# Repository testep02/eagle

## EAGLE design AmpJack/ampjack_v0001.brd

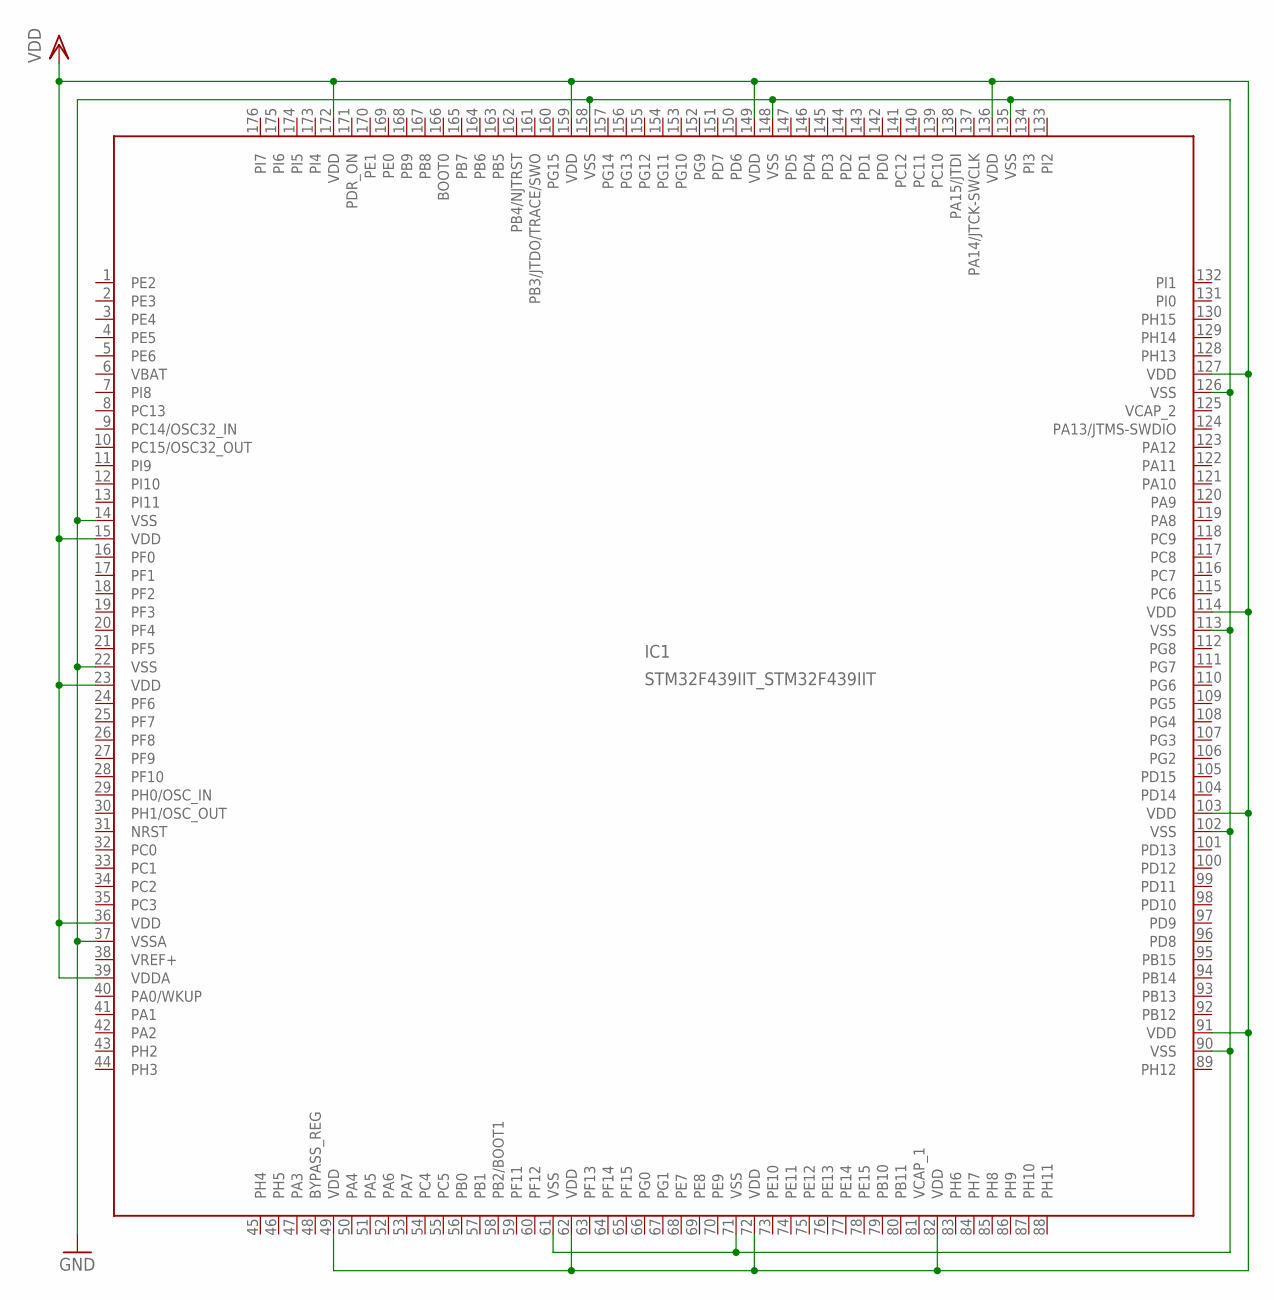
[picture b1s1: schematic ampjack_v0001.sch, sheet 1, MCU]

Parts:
IC1: STM32F439IIT_STM32F439IIT; STM32F439IIT_LQFP-176

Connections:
GND: IC1.14 (VSS), IC1.22 (VSS), IC1.37 (VSSA), IC1.61 (VSS), IC1.71 (VSS), IC1.90 (VSS), IC1.102 (VSS), IC1.113 (VSS), IC1.126 (VSS), IC1.135 (VSS), IC1.148 (VSS), IC1.158 (VSS); also elsewhere on the board
PDR_ON: IC1.171 (PDR_ON)
VBAT: IC1.6 (VBAT)
VCAP_1: IC1.81 (VCAP_1)
VCAP_2: IC1.125 (VCAP_2)
VDD: IC1.15 (VDD), IC1.23 (VDD), IC1.36 (VDD), IC1.39 (VDDA), IC1.49 (VDD), IC1.62 (VDD), IC1.72 (VDD), IC1.82 (VDD), IC1.91 (VDD), IC1.103 (VDD), IC1.114 (VDD), IC1.127 (VDD), IC1.136 (VDD), IC1.149 (VDD), IC1.159 (VDD), IC1.172 (VDD); also elsewhere on the board
VREF+: IC1.38 (VREF+)

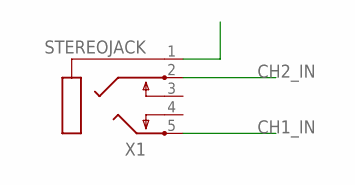
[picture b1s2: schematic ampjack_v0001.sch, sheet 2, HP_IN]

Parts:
X1: STEREOJACK; STX3100

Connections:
CH1_IN: X1.5; also elsewhere on the board
CH2_IN: X1.2; also elsewhere on the board

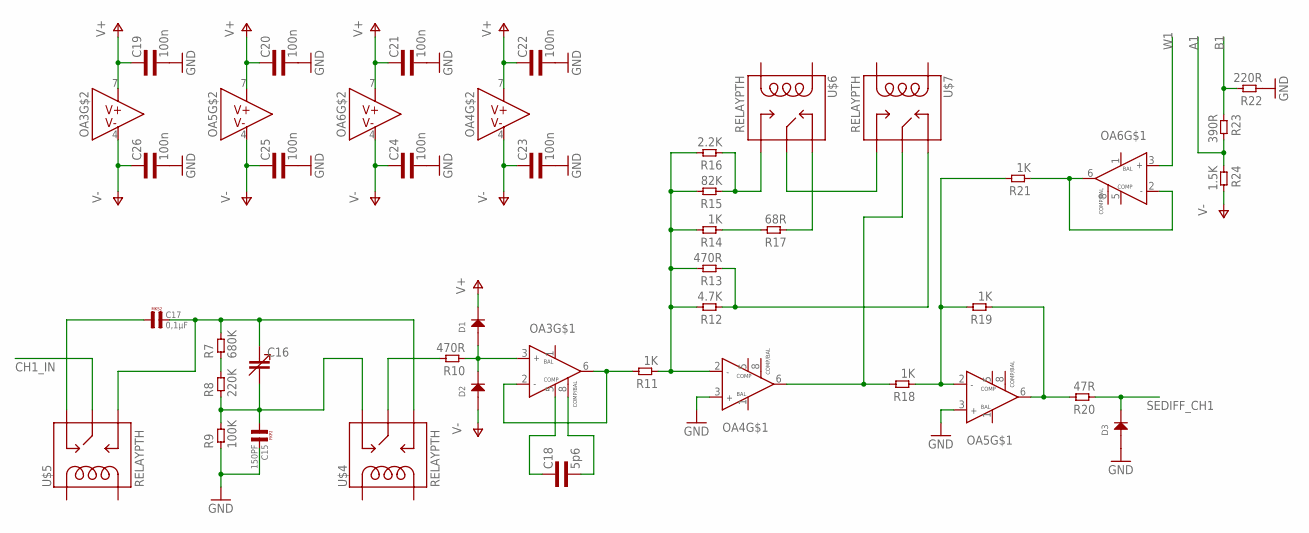
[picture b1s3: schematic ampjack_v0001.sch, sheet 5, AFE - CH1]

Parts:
C15: 150PF; R5B4K5
C16: CAP_ADJSMD; CTZ3
C17: 0,1µF; R5B3
C18: 5p6; 0603L3
C19, C20, C21, C22, C23, C24, C25, C26: 100n; 0603L3
D1, D2, D3: DIODEDO-214AC; DO-214AC
OA3, OA4, OA5, OA6: NE5534ADSOIC8; SOIC-8
R7: 680K; 0805L3
R8: 220K; 0805L3
R9: 100K; 0805L3
R10, R13: 470R; 0805L3
R11, R14, R18, R19, R21: 1K; 0805L3
R12: 4.7K; 0805L3
R15: 82K; 0805L3
R16: 2.2K; 0805L3
R17: 68R; 0805L3
R20: 47R; 0805L3
R22: 220R; 0805L3
R23: 390R; 0805L3
R24: 1.5K; 0805L3
U$4, U$5, U$6, U$7: RELAYPTH; RELAY-G5Q

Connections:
A1: R23.2, R24.1; also elsewhere on the board
B1: R22.2, R23.1; also elsewhere on the board
CH1_IN: U$5.2 (MAIN); also elsewhere on the board
GND: C15.2, C19.P$2 (2), C20.P$2 (2), C21.P$2 (2), C22.P$2 (2), C23.P$2 (2), C24.P$2 (2), C25.P$2 (2), C26.P$2 (2), D3.1 (ANODE), OA4.3 (IN+), OA5.3 (IN+), R9.1, R22.1; also elsewhere on the board
unnamed: C17.1, U$5.4 (NC)
unnamed: C16.+ (3), C17.2, R7.2, U$4.3 (NO), U$5.3 (NO)
unnamed: R7.1, R8.2
unnamed: C15.1, C16.- (4), R8.1, R9.2, U$4.4 (NC)
unnamed: R10.2, U$4.2 (MAIN)
unnamed: D1.1 (ANODE), D2.2 (CATHODE), OA3.3 (IN+), R10.1
unnamed: OA3.2 (IN-), OA3.6 (OUT), R11.2
unnamed: C18.P$1 (1), OA3.5 (COMP)
unnamed: C18.P$2 (2), OA3.8 (COMP/BAL)
unnamed: OA4.2 (IN-), R11.1, R12.2, R13.2, R14.2, R15.2, R16.2
unnamed: R12.1, R13.1, U$7.4 (NC)
unnamed: U$6.2 (MAIN), U$7.3 (NO)
unnamed: R14.1, R17.2
unnamed: R17.1, U$6.4 (NC)
unnamed: R15.1, R16.1, U$6.3 (NO)
unnamed: OA4.6 (OUT), R18.2, U$7.2 (MAIN)
unnamed: OA5.2 (IN-), R18.1, R19.2, R21.2
unnamed: OA5.6 (OUT), R19.1, R20.2
unnamed: OA6.2 (IN-), OA6.6 (OUT), R21.1
SEDIFF_CH1: D3.2 (CATHODE), R20.1; also elsewhere on the board
V+: C19.P$1 (1), C20.P$1 (1), C21.P$1 (1), C22.P$1 (1), D1.2 (CATHODE), OA3.7 (V+), OA4.7 (V+), OA5.7 (V+), OA6.7 (V+); also elsewhere on the board
V-: C23.P$1 (1), C24.P$1 (1), C25.P$1 (1), C26.P$1 (1), D2.1 (ANODE), OA3.4 (V-), OA4.4 (V-), OA5.4 (V-), OA6.4 (V-), R24.2; also elsewhere on the board
W1: OA6.3 (IN+); also elsewhere on the board

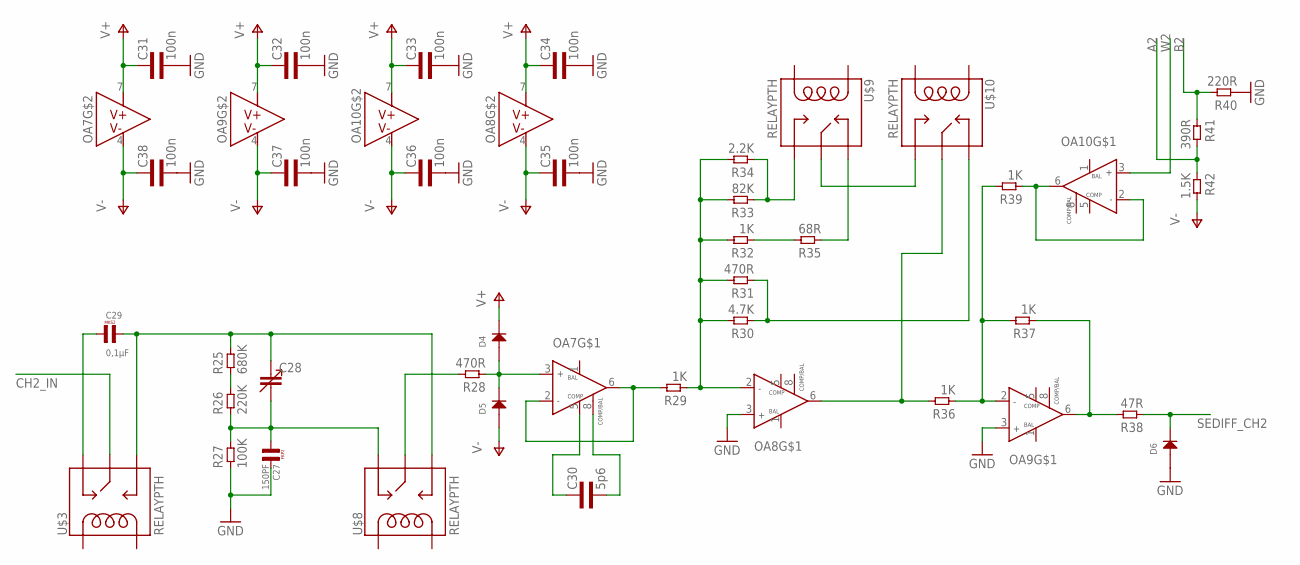
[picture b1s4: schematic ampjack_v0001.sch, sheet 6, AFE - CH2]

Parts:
C27: 150PF; R5B4K5
C28: CAP_ADJSMD; CTZ3
C29: 0,1µF; R5B3
C30: 5p6; 0603L3
C31, C32, C33, C34, C35, C36, C37, C38: 100n; 0603L3
D4, D5, D6: DIODEDO-214AC; DO-214AC
OA7, OA8, OA9, OA10: NE5534ADSOIC8; SOIC-8
R25: 680K; 0805L3
R26: 220K; 0805L3
R27: 100K; 0805L3
R28, R31: 470R; 0805L3
R29, R32, R36, R37, R39: 1K; 0805L3
R30: 4.7K; 0805L3
R33: 82K; 0805L3
R34: 2.2K; 0805L3
R35: 68R; 0805L3
R38: 47R; 0805L3
R40: 220R; 0805L3
R41: 390R; 0805L3
R42: 1.5K; 0805L3
U$3, U$8, U$9, U$10: RELAYPTH; RELAY-G5Q

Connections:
A2: R41.2, R42.1; also elsewhere on the board
B2: R40.2, R41.1; also elsewhere on the board
CH2_IN: U$3.2 (MAIN); also elsewhere on the board
GND: C27.2, C31.P$2 (2), C32.P$2 (2), C33.P$2 (2), C34.P$2 (2), C35.P$2 (2), C36.P$2 (2), C37.P$2 (2), C38.P$2 (2), D6.1 (ANODE), OA8.3 (IN+), OA9.3 (IN+), R27.1, R40.1; also elsewhere on the board
unnamed: C29.1, U$3.4 (NC)
unnamed: C28.+ (3), C29.2, R25.2, U$3.3 (NO), U$8.3 (NO)
unnamed: R25.1, R26.2
unnamed: C27.1, C28.- (4), R26.1, R27.2, U$8.4 (NC)
unnamed: R28.2, U$8.2 (MAIN)
unnamed: D4.1 (ANODE), D5.2 (CATHODE), OA7.3 (IN+), R28.1
unnamed: OA7.2 (IN-), OA7.6 (OUT), R29.2
unnamed: C30.P$1 (1), OA7.5 (COMP)
unnamed: C30.P$2 (2), OA7.8 (COMP/BAL)
unnamed: OA8.2 (IN-), R29.1, R30.2, R31.2, R32.2, R33.2, R34.2
unnamed: R30.1, R31.1, U$10.4 (NC)
unnamed: U$9.2 (MAIN), U$10.3 (NO)
unnamed: R32.1, R35.2
unnamed: R35.1, U$9.4 (NC)
unnamed: R33.1, R34.1, U$9.3 (NO)
unnamed: OA8.6 (OUT), R36.2, U$10.2 (MAIN)
unnamed: OA9.2 (IN-), R36.1, R37.2, R39.2
unnamed: OA9.6 (OUT), R37.1, R38.2
unnamed: OA10.2 (IN-), OA10.6 (OUT), R39.1
SEDIFF_CH2: D6.2 (CATHODE), R38.1; also elsewhere on the board
V+: C31.P$1 (1), C32.P$1 (1), C33.P$1 (1), C34.P$1 (1), D4.2 (CATHODE), OA7.7 (V+), OA8.7 (V+), OA9.7 (V+), OA10.7 (V+); also elsewhere on the board
V-: C35.P$1 (1), C36.P$1 (1), C37.P$1 (1), C38.P$1 (1), D5.1 (ANODE), OA7.4 (V-), OA8.4 (V-), OA9.4 (V-), OA10.4 (V-), R42.2; also elsewhere on the board
W2: OA10.3 (IN+); also elsewhere on the board

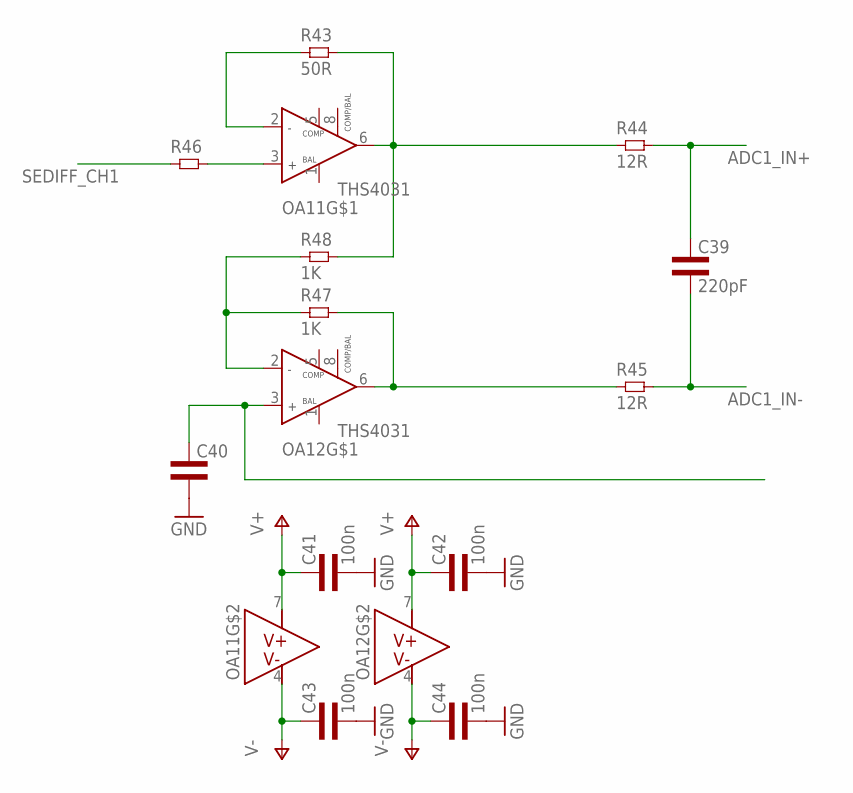
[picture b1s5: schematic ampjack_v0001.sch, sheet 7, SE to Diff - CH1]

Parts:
C39: 220pF; 0603L3
C40: CAP0603L3; 0603L3
C41, C42, C43, C44: 100n; 0603L3
OA11, OA12: THS4031; SOIC-8
R43: 50R; 0603L3
R44, R45: 12R; 0603L3
R46: RES0603L3; 0603L3
R47, R48: 1K; 0603L3

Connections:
ADC1_COMMOUT: C40.P$1 (1), OA12.3 (IN+); also elsewhere on the board
ADC1_IN+: C39.P$1 (1), R44.P$2 (2); also elsewhere on the board
ADC1_IN-: C39.P$2 (2), R45.P$2 (2); also elsewhere on the board
GND: C40.P$2 (2), C41.P$2 (2), C42.P$2 (2), C43.P$2 (2), C44.P$2 (2); also elsewhere on the board
unnamed: OA11.6 (OUT), R43.P$2 (2), R44.P$1 (1), R48.P$2 (2)
unnamed: OA12.6 (OUT), R45.P$1 (1), R47.P$2 (2)
unnamed: OA11.2 (IN-), R43.P$1 (1)
unnamed: OA11.3 (IN+), R46.P$2 (2)
unnamed: OA12.2 (IN-), R47.P$1 (1), R48.P$1 (1)
SEDIFF_CH1: R46.P$1 (1); also elsewhere on the board
V+: C41.P$1 (1), C42.P$1 (1), OA11.7 (V+), OA12.7 (V+); also elsewhere on the board
V-: C43.P$1 (1), C44.P$1 (1), OA11.4 (V-), OA12.4 (V-); also elsewhere on the board

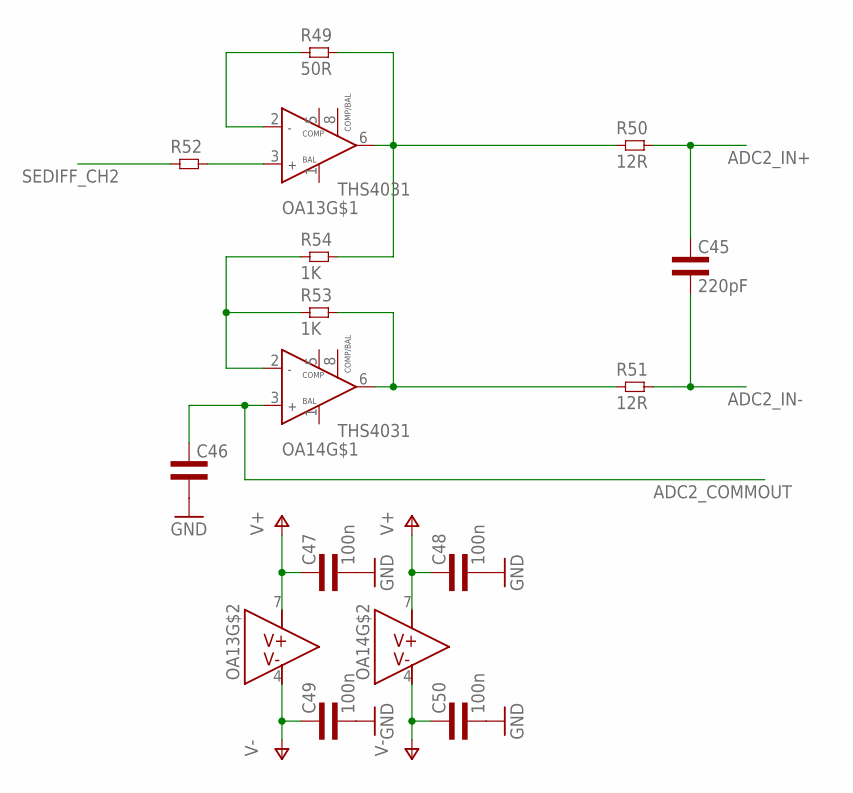
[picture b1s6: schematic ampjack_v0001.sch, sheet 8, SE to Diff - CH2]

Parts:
C45: 220pF; 0603L3
C46: CAP0603L3; 0603L3
C47, C48, C49, C50: 100n; 0603L3
OA13, OA14: THS4031; SOIC-8
R49: 50R; 0603L3
R50, R51: 12R; 0603L3
R52: RES0603L3; 0603L3
R53, R54: 1K; 0603L3

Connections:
ADC2_COMMOUT: C46.P$1 (1), OA14.3 (IN+); also elsewhere on the board
ADC2_IN+: C45.P$1 (1), R50.P$2 (2); also elsewhere on the board
ADC2_IN-: C45.P$2 (2), R51.P$2 (2); also elsewhere on the board
GND: C46.P$2 (2), C47.P$2 (2), C48.P$2 (2), C49.P$2 (2), C50.P$2 (2); also elsewhere on the board
unnamed: OA13.6 (OUT), R49.P$2 (2), R50.P$1 (1), R54.P$2 (2)
unnamed: OA14.6 (OUT), R51.P$1 (1), R53.P$2 (2)
unnamed: OA13.2 (IN-), R49.P$1 (1)
unnamed: OA13.3 (IN+), R52.P$2 (2)
unnamed: OA14.2 (IN-), R53.P$1 (1), R54.P$1 (1)
SEDIFF_CH2: R52.P$1 (1); also elsewhere on the board
V+: C47.P$1 (1), C48.P$1 (1), OA13.7 (V+), OA14.7 (V+); also elsewhere on the board
V-: C49.P$1 (1), C50.P$1 (1), OA13.4 (V-), OA14.4 (V-); also elsewhere on the board

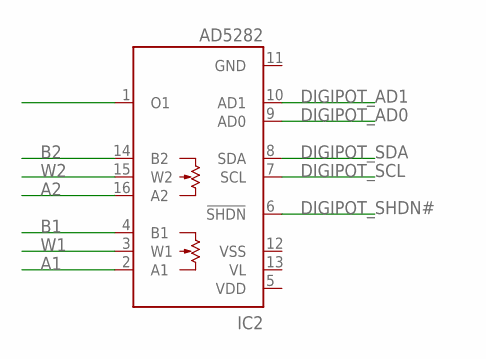
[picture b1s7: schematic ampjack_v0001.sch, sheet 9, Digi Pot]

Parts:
IC2: AD5282; TSSOP16

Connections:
A1: IC2.2 (A1); also elsewhere on the board
A2: IC2.16 (A2); also elsewhere on the board
B1: IC2.4 (B1); also elsewhere on the board
B2: IC2.14 (B2); also elsewhere on the board
DIGIPOT_AD0: IC2.9 (AD0)
DIGIPOT_AD1: IC2.10 (AD1)
DIGIPOT_SCL: IC2.7 (SCL)
DIGIPOT_SDA: IC2.8 (SDA)
DIGIPOT_SHDN#: IC2.6 (!SHDN)
GND: IC2.11 (GND); also elsewhere on the board
VDD: IC2.5 (VDD); also elsewhere on the board
VL: IC2.13 (VL)
VSS: IC2.12 (VSS)
W1: IC2.3 (W1); also elsewhere on the board
W2: IC2.15 (W2); also elsewhere on the board

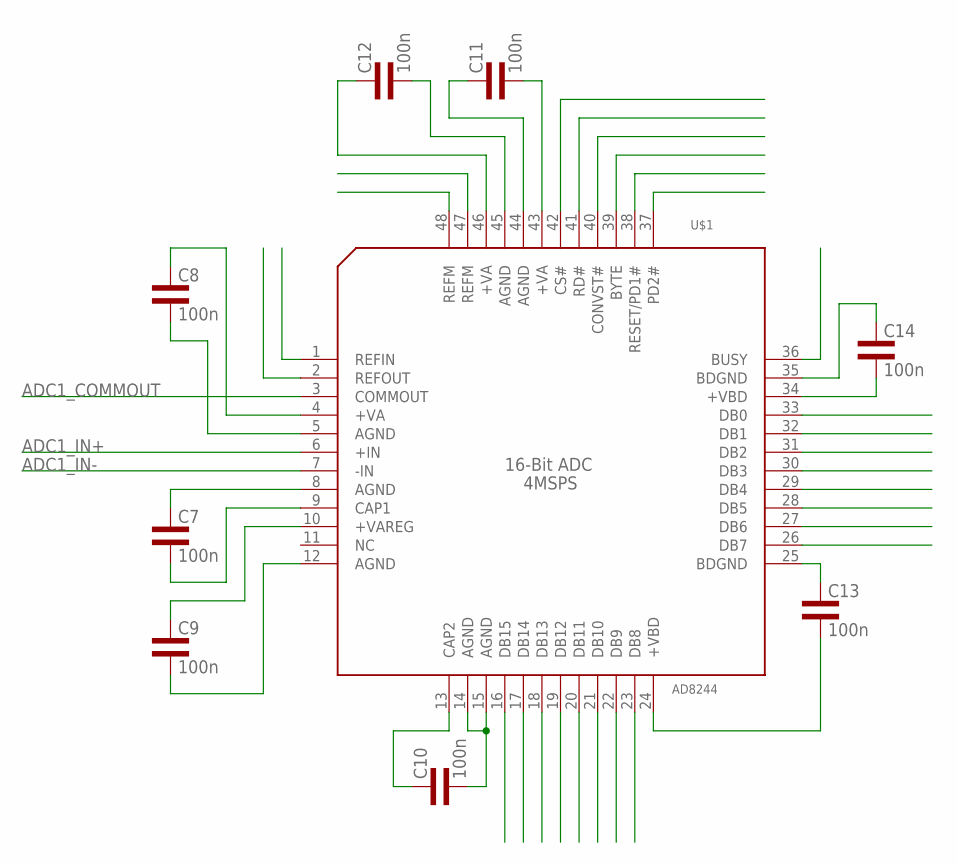
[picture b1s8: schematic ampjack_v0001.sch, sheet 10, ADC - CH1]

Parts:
C7, C8, C9, C10, C11, C12, C13, C14: 100n; 0402L3
U$1: AD8422; S-PQFP-G48

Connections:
ADC1_COMMOUT: U$1.3 (COMMOUT); also elsewhere on the board
ADC1_IN+: U$1.6 (+IN); also elsewhere on the board
ADC1_IN-: U$1.7 (-IN); also elsewhere on the board
unnamed: C8.P$2 (2), U$1.5 (AGND)
unnamed: C8.P$1 (1), U$1.4 (+VA)
unnamed: C7.P$1 (1), U$1.8 (AGND)
unnamed: C7.P$2 (2), U$1.9 (CAP1)
unnamed: C9.P$1 (1), U$1.10 (+VAREG)
unnamed: C9.P$2 (2), U$1.12 (AGND)
unnamed: C10.P$1 (1), U$1.13 (CAP2)
unnamed: C10.P$2 (2), U$1.14 (AGND), U$1.15 (AGND)
unnamed: C11.P$1 (1), U$1.44 (AGND)
unnamed: C11.P$2 (2), U$1.43 (+VA)
unnamed: C12.P$2 (2), U$1.45 (AGND)
unnamed: C12.P$1 (1), U$1.46 (+VA)
unnamed: C13.P$1 (1), U$1.25 (BDGND)
unnamed: C13.P$2 (2), U$1.24 (+VBD)
unnamed: C14.P$2 (2), U$1.34 (+VBD)
unnamed: C14.P$1 (1), U$1.35 (BDGND)

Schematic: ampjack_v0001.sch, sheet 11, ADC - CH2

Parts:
C1, C2, C3, C4, C5, C6, C51, C52: 100n; 0402L3
U$2: AD8422; S-PQFP-G48

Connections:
ADC2_COMMOUT: U$2.3 (COMMOUT); also elsewhere on the board
ADC2_IN+: U$2.6 (+IN); also elsewhere on the board
ADC2_IN-: U$2.7 (-IN); also elsewhere on the board
unnamed: C1.P$2 (2), U$2.5 (AGND)
unnamed: C1.P$1 (1), U$2.4 (+VA)
unnamed: C2.P$1 (1), U$2.8 (AGND)
unnamed: C2.P$2 (2), U$2.9 (CAP1)
unnamed: C3.P$1 (1), U$2.10 (+VAREG)
unnamed: C3.P$2 (2), U$2.12 (AGND)
unnamed: C4.P$1 (1), U$2.13 (CAP2)
unnamed: C4.P$2 (2), U$2.14 (AGND), U$2.15 (AGND)
unnamed: C5.P$1 (1), U$2.44 (AGND)
unnamed: C5.P$2 (2), U$2.43 (+VA)
unnamed: C6.P$2 (2), U$2.45 (AGND)
unnamed: C6.P$1 (1), U$2.46 (+VA)
unnamed: C51.P$1 (1), U$2.25 (BDGND)
unnamed: C51.P$2 (2), U$2.24 (+VBD)
unnamed: C52.P$2 (2), U$2.34 (+VBD)
unnamed: C52.P$1 (1), U$2.35 (BDGND)

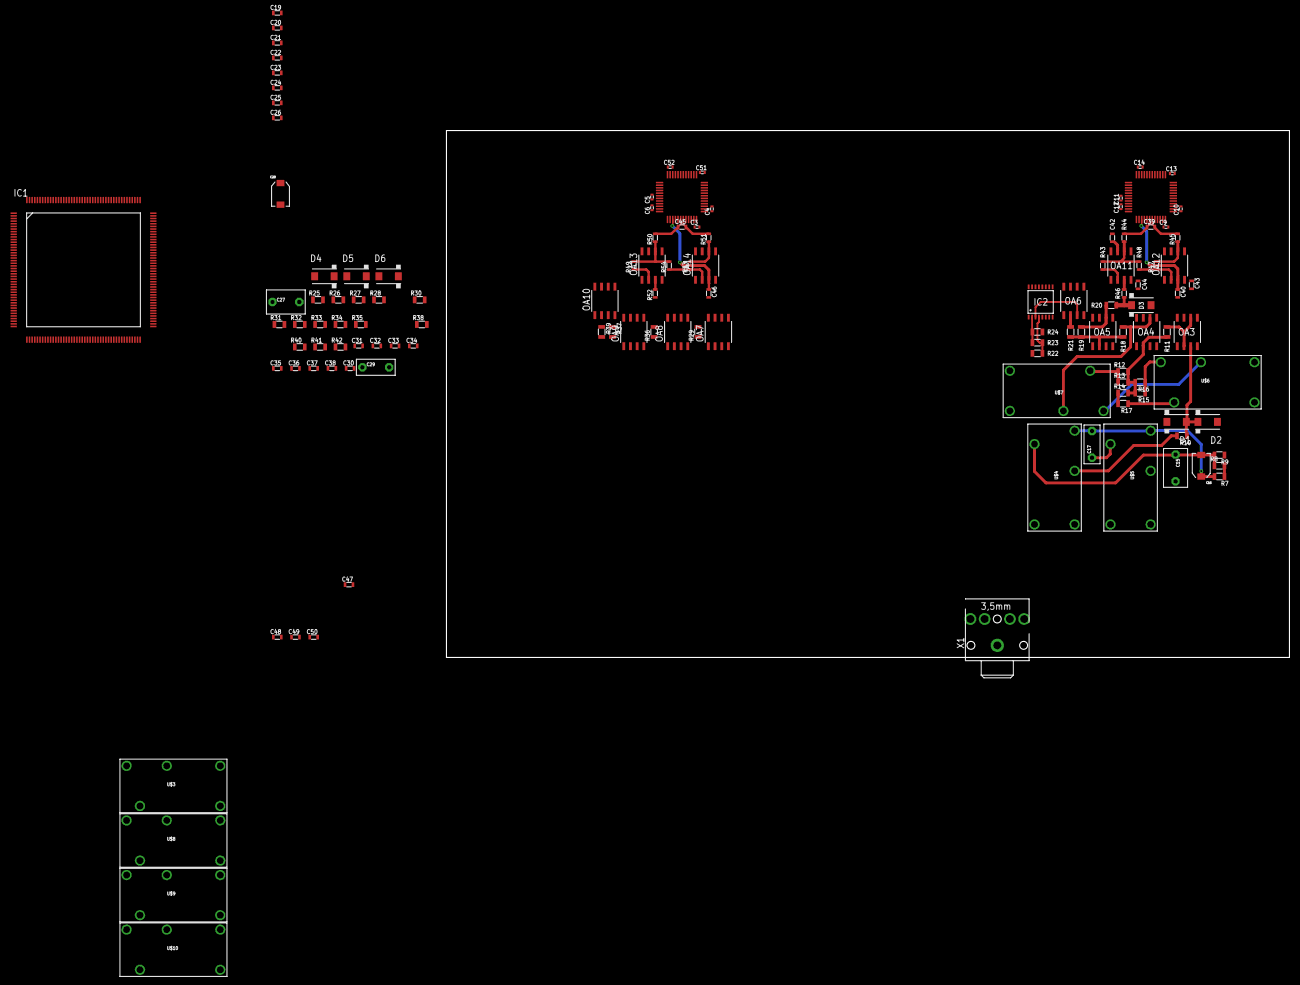
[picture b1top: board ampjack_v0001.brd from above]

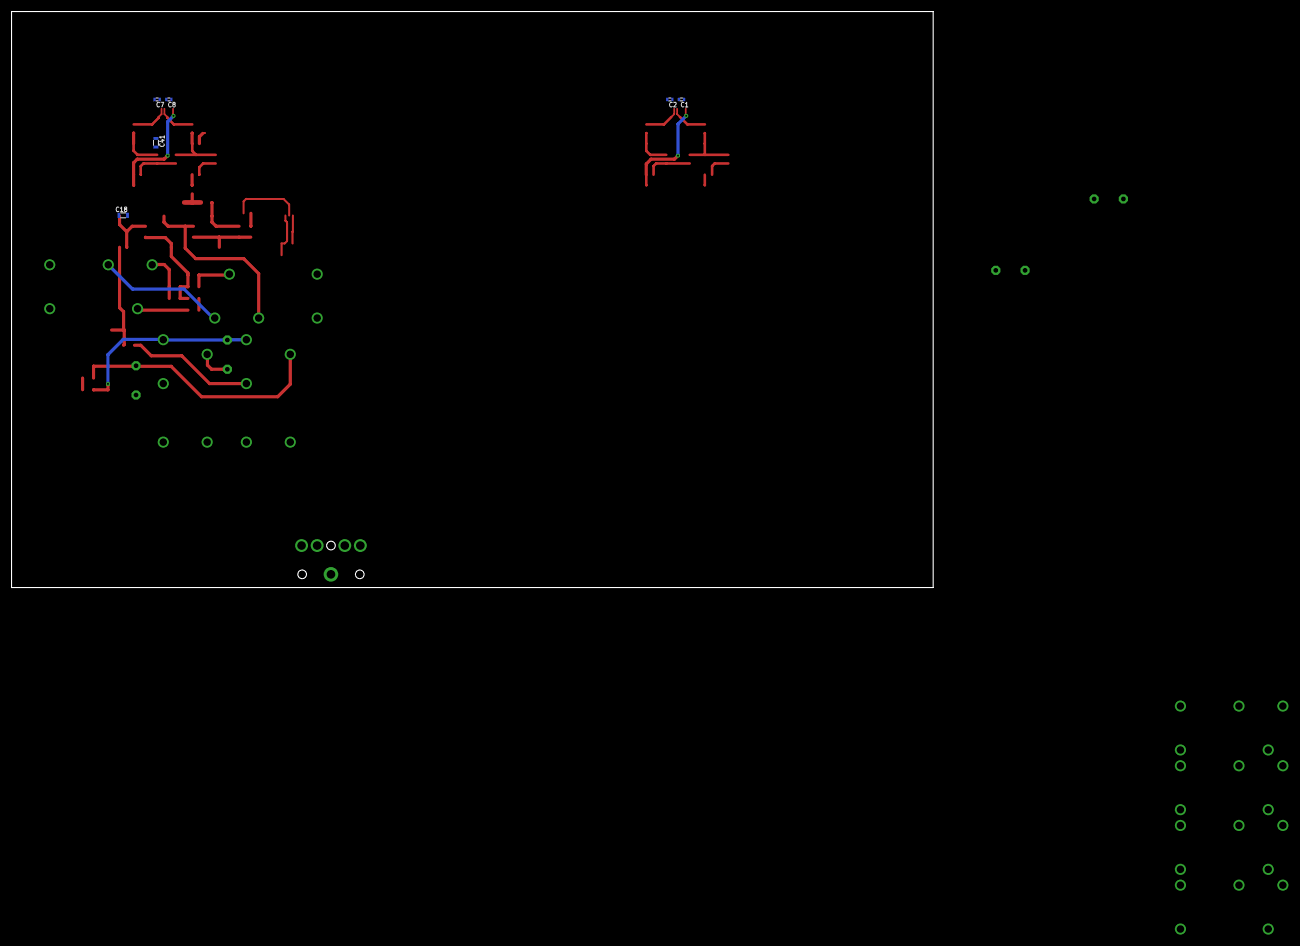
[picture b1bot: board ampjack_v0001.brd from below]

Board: 2 copper layers, 160.0 x 100.0 mm, 131 parts (6 on the bottom side), 100 nets.

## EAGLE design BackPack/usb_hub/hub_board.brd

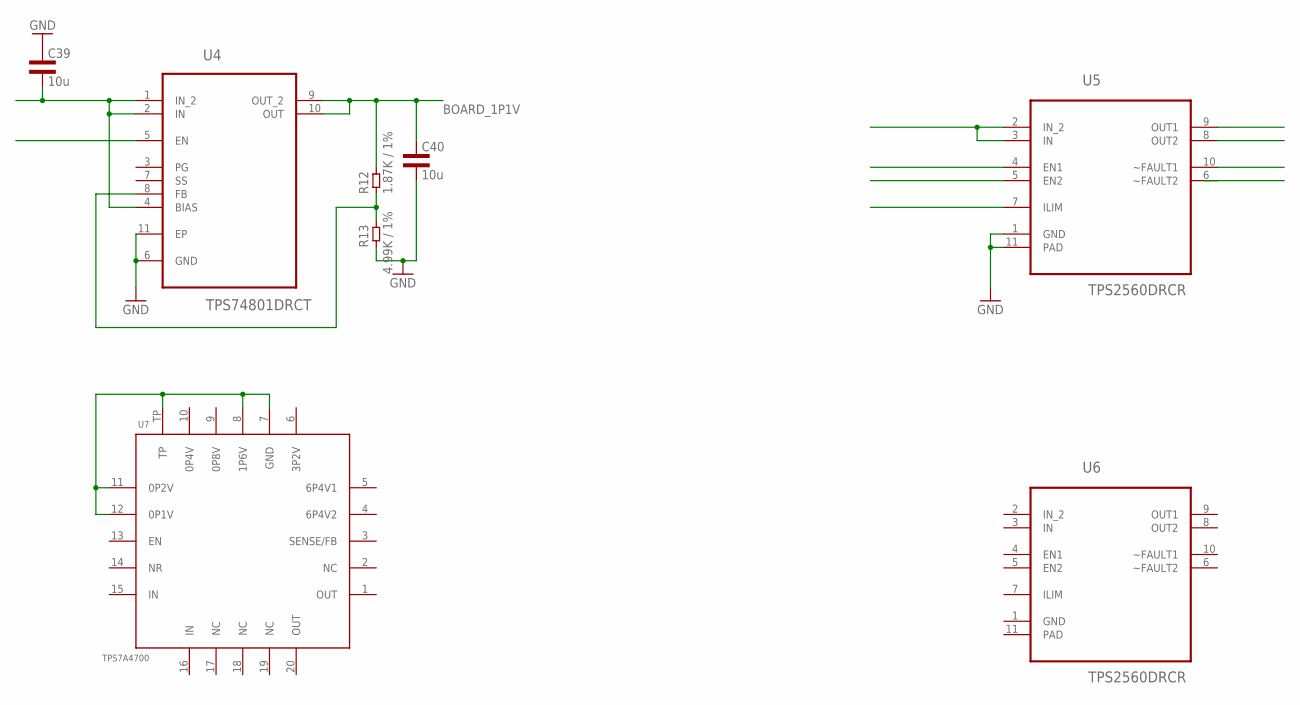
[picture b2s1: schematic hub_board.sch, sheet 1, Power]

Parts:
C39, C40: 10u; 0805L3
R12: 1.87K / 1%; 0603L3
R13: 4.99K / 1%; 0603L3
U4: TPS74801DRCT; SON50P300X300X100-11N
U5, U6: TPS2560DRCR; SON50P300X300X100-11N
U7: TPS7A4700; VQFN-20

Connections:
BOARD_1P1V: C40.1, R12.P$2 (2), U4.9 (OUT_2), U4.10 (OUT)
GND: C39.1, C40.2, R13.P$1 (1), U4.6 (GND), U4.11 (EP), U5.1 (GND), U5.11 (PAD); also elsewhere on the board
IN: U6.3 (IN)
IN_2: U6.2 (IN_2)
unnamed: C39.2, U4.1 (IN_2), U4.2 (IN), U4.4 (BIAS)
unnamed: U5.2 (IN_2), U5.3 (IN)
unnamed: R12.P$1 (1), R13.P$2 (2), U4.8 (FB)
unnamed: U7.7 (GND), U7.8 (1P6V), U7.11 (0P2V), U7.12 (0P1V), U7.TP

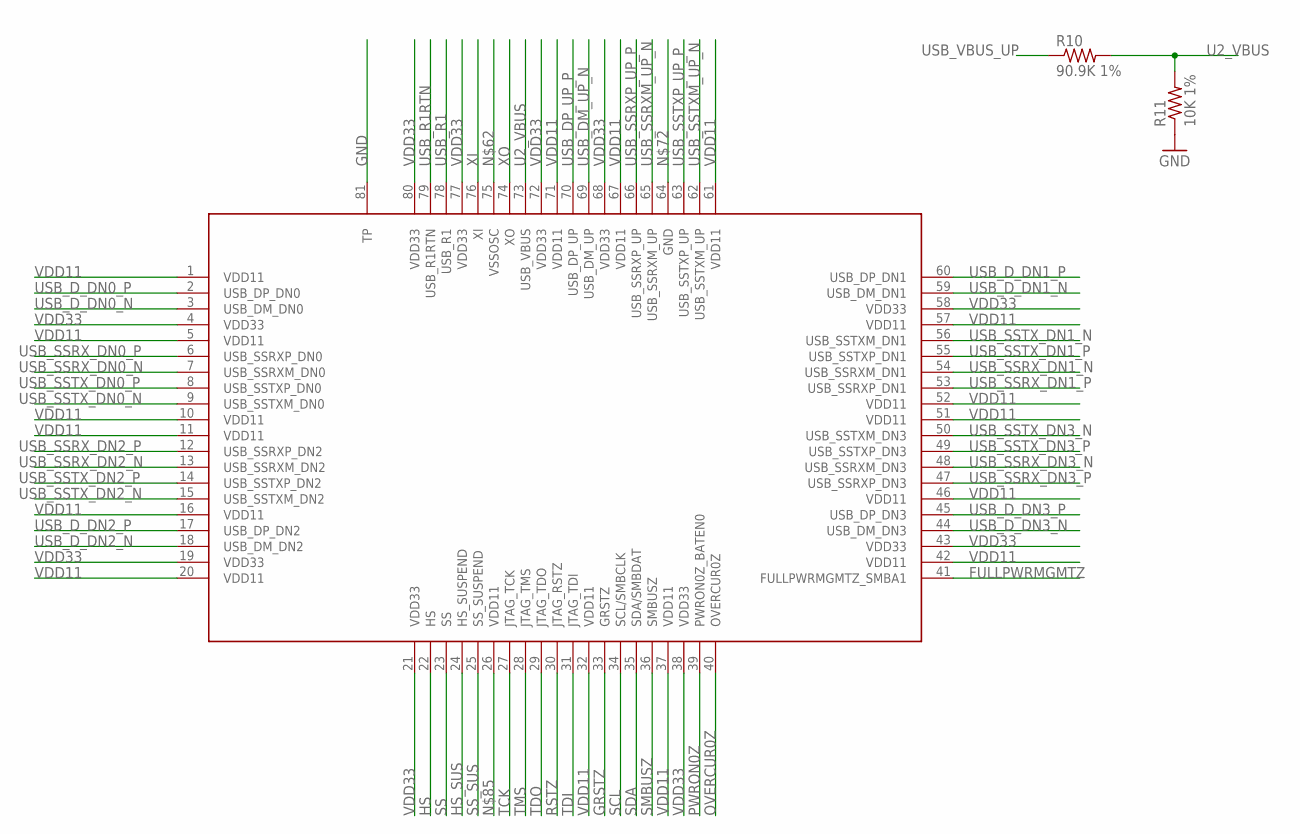
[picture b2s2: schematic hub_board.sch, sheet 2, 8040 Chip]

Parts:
R10: 90.9K 1%; R0603
R11: 10K 1%; R0603
U2: TUSB8040PFP; S-PQFP-G80

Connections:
FULLPWRMGMTZ: U2.41 (FULLPWRMGMTZ_SMBA1)
GND: R11.1, U2.81 (TP); also elsewhere on the board
GRSTZ: U2.33 (GRSTZ)
HS: U2.22 (HS); also elsewhere on the board
HS_SUS: U2.24 (HS_SUSPEND); also elsewhere on the board
OVERCUR0Z: U2.40 (OVERCUR0Z)
PWRON0Z: U2.39 (PWRON0Z_BATEN0)
RSTZ: U2.30 (JTAG_RSTZ)
SCL: U2.34 (SCL/SMBCLK)
SDA: U2.35 (SDA/SMBDAT)
SMBUSZ: U2.36 (SMBUSZ)
SS: U2.23 (SS); also elsewhere on the board
SS_SUS: U2.25 (SS_SUSPEND); also elsewhere on the board
TCK: U2.27 (JTAG_TCK)
TDI: U2.31 (JTAG_TDI)
TDO: U2.29 (JTAG_TDO)
TMS: U2.28 (JTAG_TMS)
U2_VBUS: R10.2, R11.2, U2.73 (USB_VBUS)
USB_DM_UP_N: U2.69 (USB_DM_UP); also elsewhere on the board
USB_DP_UP_P: U2.70 (USB_DP_UP); also elsewhere on the board
USB_D_DN0_N: U2.3 (USB_DM_DN0); also elsewhere on the board
USB_D_DN0_P: U2.2 (USB_DP_DN0); also elsewhere on the board
USB_D_DN1_N: U2.59 (USB_DM_DN1); also elsewhere on the board
USB_D_DN1_P: U2.60 (USB_DP_DN1); also elsewhere on the board
USB_D_DN2_N: U2.18 (USB_DM_DN2); also elsewhere on the board
USB_D_DN2_P: U2.17 (USB_DP_DN2); also elsewhere on the board
USB_D_DN3_N: U2.44 (USB_DM_DN3); also elsewhere on the board
USB_D_DN3_P: U2.45 (USB_DP_DN3); also elsewhere on the board
USB_R1: U2.78 (USB_R1)
USB_R1RTN: U2.79 (USB_R1RTN)
USB_SSRXM_UP_N: U2.65 (USB_SSRXM_UP)
USB_SSRXP_UP_P: U2.66 (USB_SSRXP_UP)
USB_SSRX_DN0_N: U2.7 (USB_SSRXM_DN0); also elsewhere on the board
USB_SSRX_DN0_P: U2.6 (USB_SSRXP_DN0); also elsewhere on the board
USB_SSRX_DN1_N: U2.54 (USB_SSRXM_DN1); also elsewhere on the board
USB_SSRX_DN1_P: U2.53 (USB_SSRXP_DN1); also elsewhere on the board
USB_SSRX_DN2_N: U2.13 (USB_SSRXM_DN2); also elsewhere on the board
USB_SSRX_DN2_P: U2.12 (USB_SSRXP_DN2); also elsewhere on the board
USB_SSRX_DN3_N: U2.48 (USB_SSRXM_DN3); also elsewhere on the board
USB_SSRX_DN3_P: U2.47 (USB_SSRXP_DN3); also elsewhere on the board
USB_SSTXM_UP_N: U2.62 (USB_SSTXM_UP)
USB_SSTXP_UP_P: U2.63 (USB_SSTXP_UP)
USB_SSTX_DN0_N: U2.9 (USB_SSTXM_DN0); also elsewhere on the board
USB_SSTX_DN0_P: U2.8 (USB_SSTXP_DN0); also elsewhere on the board
USB_SSTX_DN1_N: U2.56 (USB_SSTXM_DN1); also elsewhere on the board
USB_SSTX_DN1_P: U2.55 (USB_SSTXP_DN1); also elsewhere on the board
USB_SSTX_DN2_N: U2.15 (USB_SSTXM_DN2); also elsewhere on the board
USB_SSTX_DN2_P: U2.14 (USB_SSTXP_DN2); also elsewhere on the board
USB_SSTX_DN3_N: U2.50 (USB_SSTXM_DN3); also elsewhere on the board
USB_SSTX_DN3_P: U2.49 (USB_SSTXP_DN3); also elsewhere on the board
USB_VBUS_UP: R10.1
VDD11: U2.1 (VDD11), U2.5 (VDD11), U2.10 (VDD11), U2.11 (VDD11), U2.16 (VDD11), U2.20 (VDD11), U2.32 (VDD11), U2.37 (VDD11), U2.42 (VDD11), U2.46 (VDD11), U2.51 (VDD11), U2.52 (VDD11), U2.57 (VDD11), U2.61 (VDD11), U2.67 (VDD11), U2.71 (VDD11); also elsewhere on the board
VDD33: U2.4 (VDD33), U2.19 (VDD33), U2.21 (VDD33), U2.38 (VDD33), U2.43 (VDD33), U2.58 (VDD33), U2.68 (VDD33), U2.72 (VDD33), U2.77 (VDD33), U2.80 (VDD33); also elsewhere on the board
XI: U2.76 (XI)
XO: U2.74 (XO)

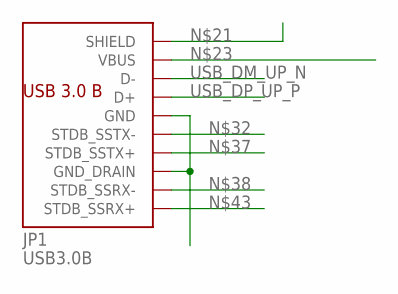
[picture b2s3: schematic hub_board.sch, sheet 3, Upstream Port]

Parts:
JP1: USB3.0B; AMPHENOLUSB3.0B

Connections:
unnamed: JP1.10@1 (SHIELD), JP1.10@2 (SHIELD)
unnamed: JP1.4 (GND), JP1.7 (GND_DRAIN)
USB_DM_UP_N: JP1.2 (D-); also elsewhere on the board
USB_DP_UP_P: JP1.3 (D+); also elsewhere on the board

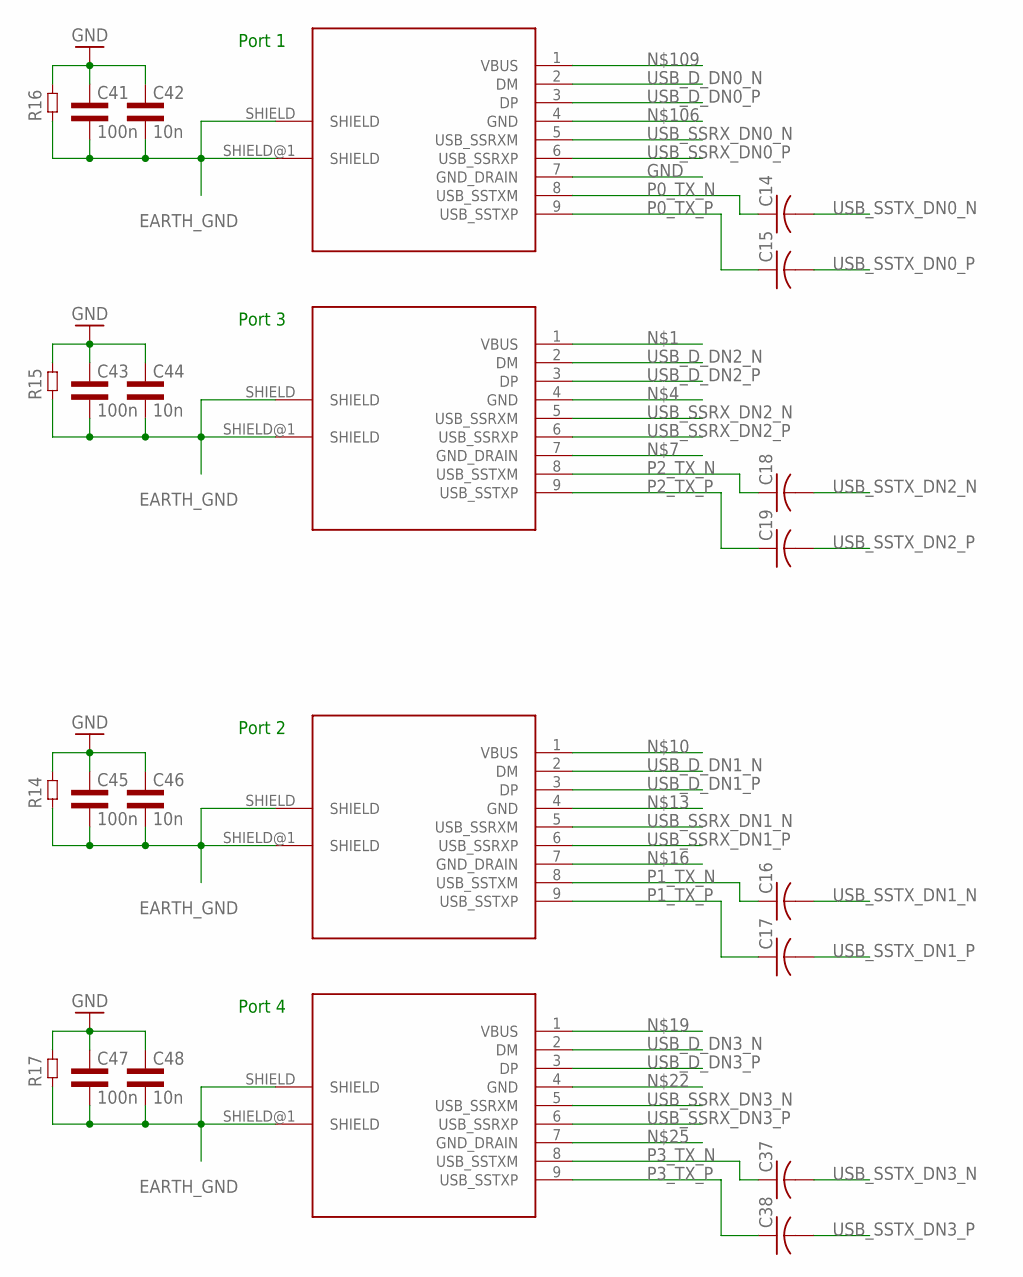
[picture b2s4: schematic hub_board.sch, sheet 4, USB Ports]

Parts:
C14, C15, C16, C17, C18, C19, C37, C38: C-USC0201; C0201
C41, C43, C45, C47: 100n; 0603L3
C42, C44, C46, C48: 10n; 0603L3
R14, R15, R16, R17: RES0603L3; 0603L3
U$1, U$3, U$4, U$5: USB_SS_CONN_TYPE_A; R_A_DIP

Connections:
EARTH_GND: C41.P$2 (2), C42.P$2 (2), C43.P$2 (2), C44.P$2 (2), C45.P$2 (2), C46.P$2 (2), C47.P$2 (2), C48.P$2 (2), R14.P$1 (1), R15.P$1 (1), R16.P$1 (1), R17.P$1 (1), U$1.SHIELD, U$1.SHIELD@1 (SHIELD), U$3.SHIELD, U$3.SHIELD@1 (SHIELD), U$4.SHIELD, U$4.SHIELD@1 (SHIELD), U$5.SHIELD, U$5.SHIELD@1 (SHIELD)
GND: C41.P$1 (1), C42.P$1 (1), C43.P$1 (1), C44.P$1 (1), C45.P$1 (1), C46.P$1 (1), C47.P$1 (1), C48.P$1 (1), R14.P$2 (2), R15.P$2 (2), R16.P$2 (2), R17.P$2 (2), U$1.7 (GND_DRAIN); also elsewhere on the board
P0_TX_N: C14.1, U$1.8 (USB_SSTXM)
P0_TX_P: C15.1, U$1.9 (USB_SSTXP)
P1_TX_N: C16.1, U$4.8 (USB_SSTXM)
P1_TX_P: C17.1, U$4.9 (USB_SSTXP)
P2_TX_N: C18.1, U$3.8 (USB_SSTXM)
P2_TX_P: C19.1, U$3.9 (USB_SSTXP)
P3_TX_N: C37.1, U$5.8 (USB_SSTXM)
P3_TX_P: C38.1, U$5.9 (USB_SSTXP)
USB_D_DN0_N: U$1.2 (DM); also elsewhere on the board
USB_D_DN0_P: U$1.3 (DP); also elsewhere on the board
USB_D_DN1_N: U$4.2 (DM); also elsewhere on the board
USB_D_DN1_P: U$4.3 (DP); also elsewhere on the board
USB_D_DN2_N: U$3.2 (DM); also elsewhere on the board
USB_D_DN2_P: U$3.3 (DP); also elsewhere on the board
USB_D_DN3_N: U$5.2 (DM); also elsewhere on the board
USB_D_DN3_P: U$5.3 (DP); also elsewhere on the board
USB_SSRX_DN0_N: U$1.5 (USB_SSRXM); also elsewhere on the board
USB_SSRX_DN0_P: U$1.6 (USB_SSRXP); also elsewhere on the board
USB_SSRX_DN1_N: U$4.5 (USB_SSRXM); also elsewhere on the board
USB_SSRX_DN1_P: U$4.6 (USB_SSRXP); also elsewhere on the board
USB_SSRX_DN2_N: U$3.5 (USB_SSRXM); also elsewhere on the board
USB_SSRX_DN2_P: U$3.6 (USB_SSRXP); also elsewhere on the board
USB_SSRX_DN3_N: U$5.5 (USB_SSRXM); also elsewhere on the board
USB_SSRX_DN3_P: U$5.6 (USB_SSRXP); also elsewhere on the board
USB_SSTX_DN0_N: C14.2; also elsewhere on the board
USB_SSTX_DN0_P: C15.2; also elsewhere on the board
USB_SSTX_DN1_N: C16.2; also elsewhere on the board
USB_SSTX_DN1_P: C17.2; also elsewhere on the board
USB_SSTX_DN2_N: C18.2; also elsewhere on the board
USB_SSTX_DN2_P: C19.2; also elsewhere on the board
USB_SSTX_DN3_N: C37.2; also elsewhere on the board
USB_SSTX_DN3_P: C38.2; also elsewhere on the board

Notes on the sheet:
Port 3
Port 2
Port 4
Port 1

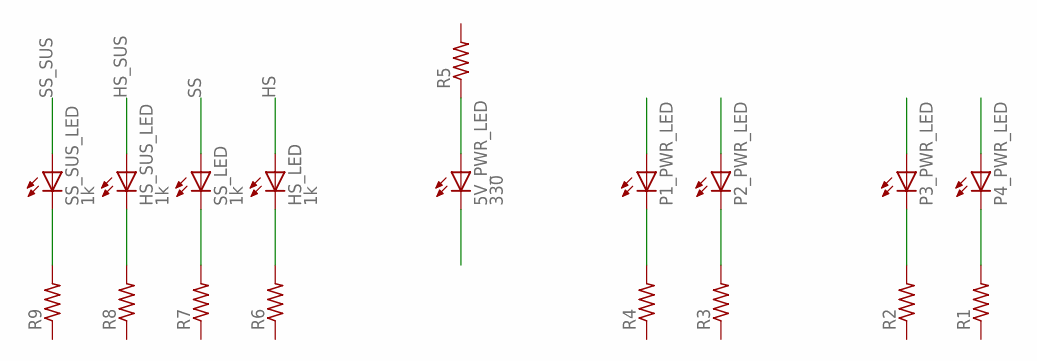
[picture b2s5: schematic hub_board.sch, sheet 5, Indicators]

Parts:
5V_PWR_LED: 330; CHIP-LED0603
HS_LED: 1k; CHIP-LED0603
HS_SUS_LED: 1k; CHIP-LED0603
P1_PWR_LED, P2_PWR_LED, P3_PWR_LED, P4_PWR_LED: LEDCHIP-LED0603; CHIP-LED0603
R1, R2, R3, R4, R5, R6, R7, R8, R9: R-US_R0603; R0603
SS_LED: 1k; CHIP-LED0603
SS_SUS_LED: 1k; CHIP-LED0603

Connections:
HS: HS_LED.A; also elsewhere on the board
HS_SUS: HS_SUS_LED.A; also elsewhere on the board
unnamed: 5V_PWR_LED.A, R5.1
unnamed: P4_PWR_LED.C, R1.2
unnamed: P3_PWR_LED.C, R2.2
unnamed: P2_PWR_LED.C, R3.2
unnamed: HS_LED.C, R6.2
unnamed: R7.2, SS_LED.C
unnamed: HS_SUS_LED.C, R8.2
unnamed: R9.2, SS_SUS_LED.C
unnamed: P1_PWR_LED.C, R4.2
SS: SS_LED.A; also elsewhere on the board
SS_SUS: SS_SUS_LED.A; also elsewhere on the board

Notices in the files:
parts and their libraries:
SparkFun-Passives: Licensing: CC v3.0 Share-Alike You are welcome to use this library for commercial purposes.
